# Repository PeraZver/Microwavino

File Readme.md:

# Microwavino

Microwave circuits for makers!

Based on  Maxim Integrated PLL chip MAX2871 with integrated VCO. 
Sowftware is based on my previous project [Microwave Transmitter](https://github.com/PeraZver/Microwave-Transmitter).

Pero, September 2017

(https://www.helentronica.com)

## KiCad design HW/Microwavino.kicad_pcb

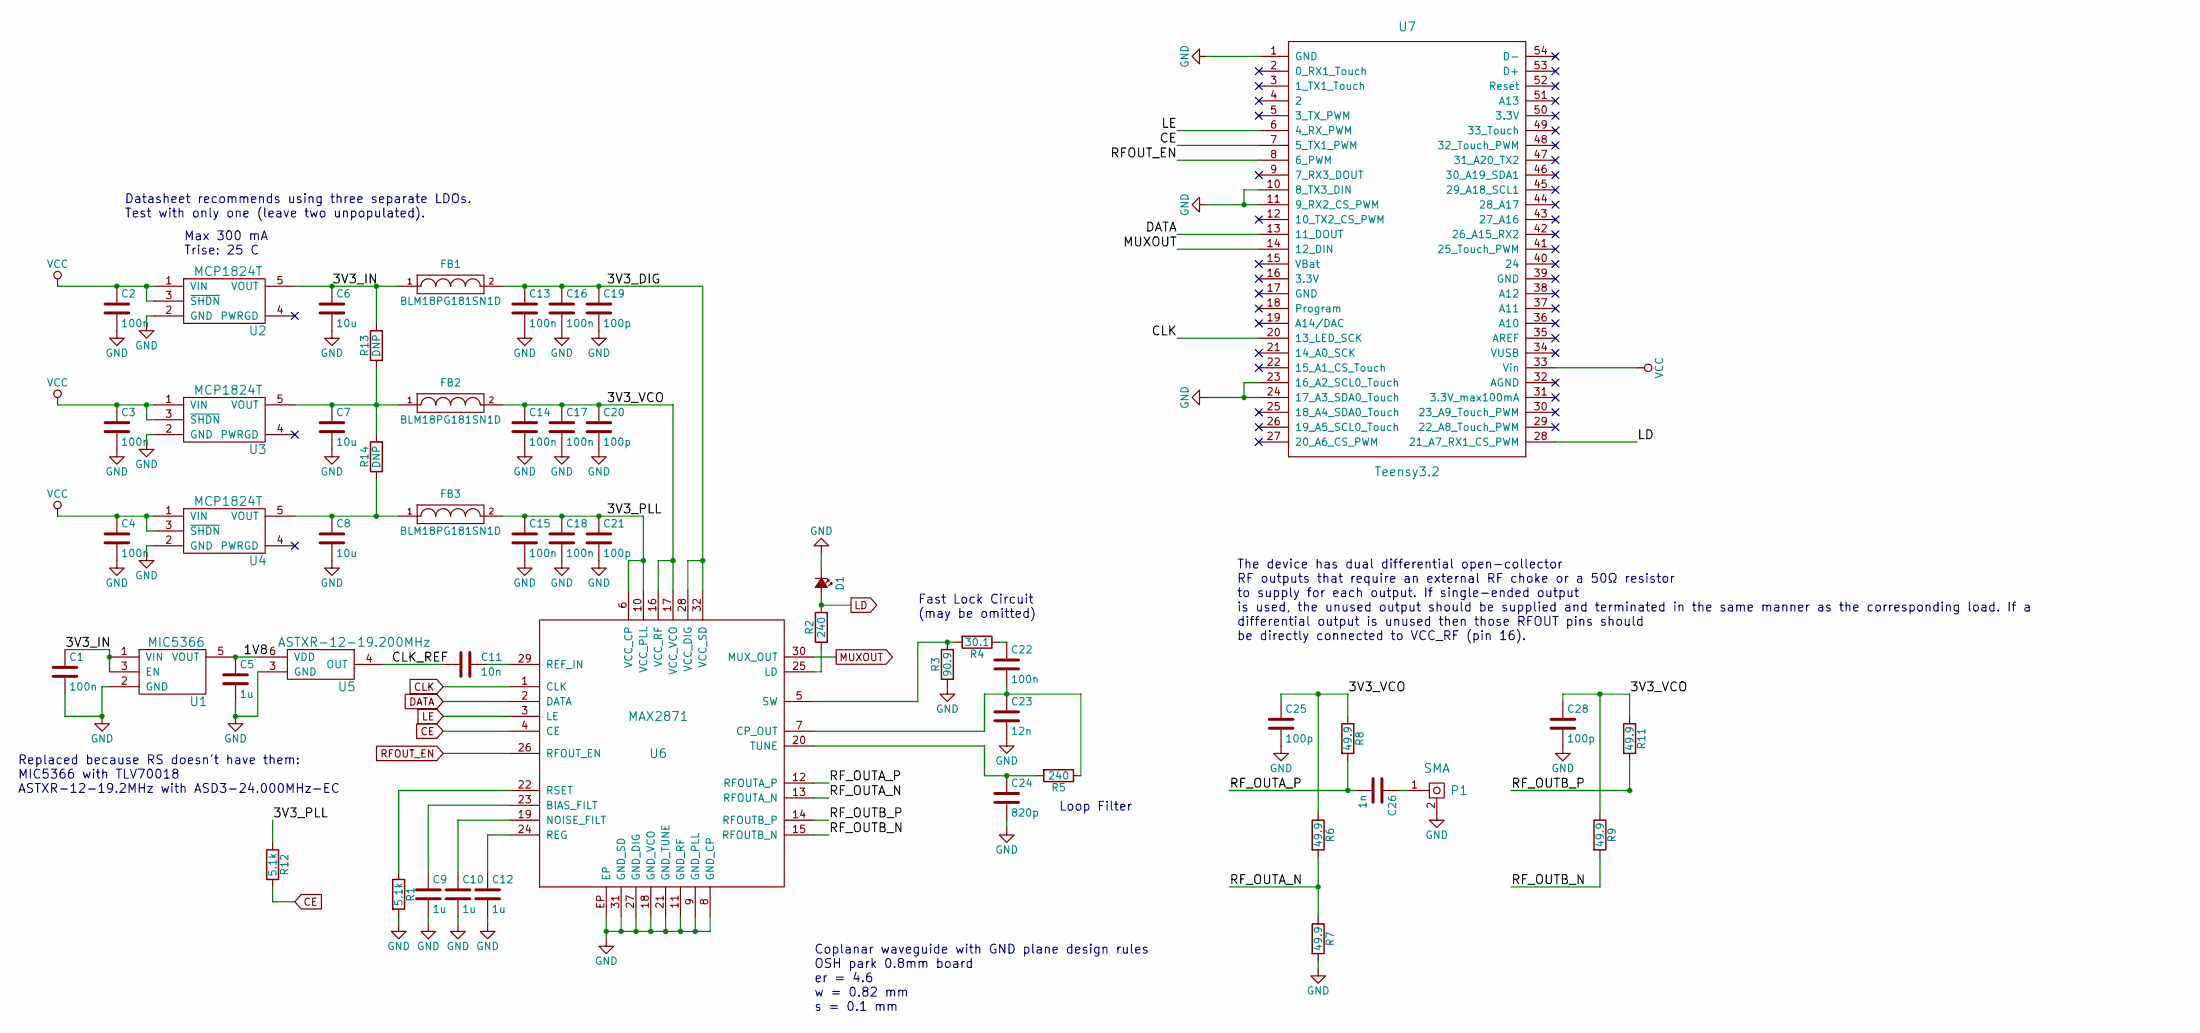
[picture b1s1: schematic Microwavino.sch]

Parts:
C1: 100n; C_0603b
C2, C3, C4, C13, C14, C15, C16, C17, C18, C22: 100n; C_0402b
C5: 1u; C_0603b
C6, C7, C8: 10u; C_0805b
C9, C10, C12: 1u; C_0402b
C11: 10n; C_0402b
C19, C20, C21, C25, C28: 100p; C_0402b
C23: 12n; C_0402b
C24: 820p; C_0402b
C26: 1n; C_0402b
D1: LED_Small_ALT; LED_0603
FB1, FB2, FB3: BLM18PG181SN1D; C_0603b
P1: SMA; CONSMA003.062
R1, R12: 5.1k; R_0402b
R2, R5: 240; R_0402b
R3: 90.9; R_0402b
R4: 30.1; R_0402b
R6, R7, R8, R9, R11: 49.9; R_0402b
R13, R14: DNP; R_0402b
U1: MIC5366; SOT-353_SC-70-5
U2, U3, U4: MCP1824T; SOT-23-5
U5: ASTXR-12-19.200MHz; ASTRX-12
U6: MAX2871; TQFN-32
U7: Teensy3.2; Teensy30_31_32_LC_modified

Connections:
/1V8: C5.1, U1.5 (VOUT), U5.6 (VDD)
/3V3_DIG: C13.1, C16.1, C19.1, FB1.2, U6.28 (VCC_DIG), U6.32 (VCC_SD)
/3V3_IN: C1.1, C6.1, FB1.1, R13.2, U1.1 (VIN), U1.3 (EN), U2.5 (VOUT)
/3V3_PLL: C15.1, C18.1, C21.1, FB3.2, R12.1, U6.6 (VCC_CP), U6.10 (VCC_PLL)
/3V3_VCO: C14.1, C17.1, C20.1, C25.1, C28.1, FB2.2, R6.1, R8.1, R9.1, R11.1, U6.16 (VCC_RF), U6.17 (VCC_VCO)
/CLK_REF: C11.2, U5.4 (OUT)
/RF_OUTA_N: R6.2, R7.1, U6.13 (RFOUTA_N)
/RF_OUTA_P: C26.2, R8.2, U6.12 (RFOUTA_P)
/RF_OUTB_N: R9.2, U6.15 (RFOUTB_N)
/RF_OUTB_P: R11.2, U6.14 (RFOUTB_P)
CE: R12.2, U6.4 (CE), U7.7 (5_TX1_PWM)
CLK: U6.1 (CLK), U7.20 (13_LED_SCK)
DATA: U6.2 (DATA), U7.13 (11_DOUT)
GND: C1.2, C2.2, C3.2, C4.2, C5.2, C6.2, C7.2, C8.2, C9.2, C10.2, C12.2, C13.2, C14.2, C15.2, C16.2, C17.2, C18.2, C19.2, C20.2, C21.2, C23.2, C24.2, C25.2, C28.2, D1.1 (K), P1.2, R1.2, R3.1, R7.2, U1.2 (GND), U2.2 (GND), U3.2 (GND), U4.2 (GND), U5.3 (GND), U6.8 (GND_CP), U6.9 (GND_PLL), U6.11 (GND_RF), U6.18 (GND_VCO), U6.21 (GND_TUNE), U6.27 (GND_DIG), U6.31 (GND_SD), U6.EP, U7.1 (GND), U7.10 (8_TX3_DIN), U7.11 (9_RX2_CS_PWM), U7.23 (16_A2_SCL0_Touch), U7.24 (17_A3_SDA0_Touch)
LD: D1.2 (A), R2.2, U7.28 (21_A7_RX1_CS_PWM)
LE: U6.3 (LE), U7.6 (4_RX_PWM)
MUXOUT: U6.30 (MUX_OUT), U7.14 (12_DIN)
unnamed: C7.1, FB2.1, R13.1, R14.2, U3.5 (VOUT)
unnamed: C8.1, FB3.1, R14.1, U4.5 (VOUT)
unnamed: C9.1, U6.23 (BIAS_FILT)
unnamed: C10.1, U6.19 (NOISE_FILT)
unnamed: C11.1, U6.29 (REF_IN)
unnamed: C12.1, U6.24 (REG)
unnamed: C22.1, R4.1
unnamed: C22.2, C23.1, R5.1, U6.7 (CP_OUT)
unnamed: C24.1, R5.2, U6.20 (TUNE)
unnamed: C26.1, P1.1
unnamed: R1.1, U6.22 (RSET)
unnamed: R2.1, U6.25 (LD)
unnamed: R3.2, R4.2, U6.5 (SW)
RFOUT_EN: U6.26 (RFOUT_EN), U7.8 (6_PWM)
VCC: C2.1, C3.1, C4.1, U2.1 (VIN), U2.3 (~SHDN), U3.1 (VIN), U3.3 (~SHDN), U4.1 (VIN), U4.3 (~SHDN), U7.33 (Vin)

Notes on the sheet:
Max 300 mA Trise: 25 C
Datasheet recommends using three separate LDOs. Test with only one (leave two unpopulated).
The device has dual differential open-collector RF outputs that require an external RF choke or a 50Ω resistor to supply for each output. If single-ended output is used, the unused output should be supplied and terminated in the same manner as the corresponding load. If a differential output is unu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
Loop Filter
Fast Lock Circuit (may be omitted)
Coplanar waveguide with GND plane design rules OSH park 0.8mm board er = 4.6 w = 0.82 mm s = 0.1 mm
Replaced because RS doesn't have them: MIC5366 with TLV70018 ASTXR-12-19.2MHz with ASD3-24.000MHz-EC

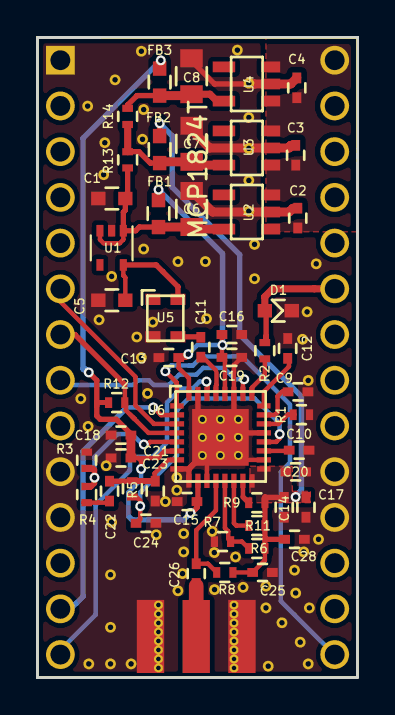
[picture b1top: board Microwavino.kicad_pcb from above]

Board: 2 copper layers, 17.8 x 35.6 mm, 52 parts (0 on the bottom side), 32 nets.

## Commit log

2017-09-06 init commit
2017-09-07 testing connection
2017-09-07 prelim placement
2017-09-07 before placement
2017-09-08 prelim layout
2017-09-08 route all except power
2017-09-11 layout completed v1.0
2017-09-11 rm teensy folders
2017-09-11 drc pass
2017-09-11 rm bak files again
2017-09-11 added footprint SOT-323-70-sc-5
2017-09-12 released and ordered
2017-10-12 added sw and wiki
2017-10-12 rm wiki
2017-10-13 back to arduino
2017-10-15 fixed error, modified script
2017-10-15 readme
2017-10-15 add serial port as python script argument
